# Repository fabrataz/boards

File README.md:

# boards

You'll find here various kicad projects
## Digital:
* digital/SO16SO18W - breakboard for SMD SOIC-16 and SOIC-18W circuits.

## Analog: 
* analog/arpege  - schematic of active electronics (for Passion and Arpege guitars)

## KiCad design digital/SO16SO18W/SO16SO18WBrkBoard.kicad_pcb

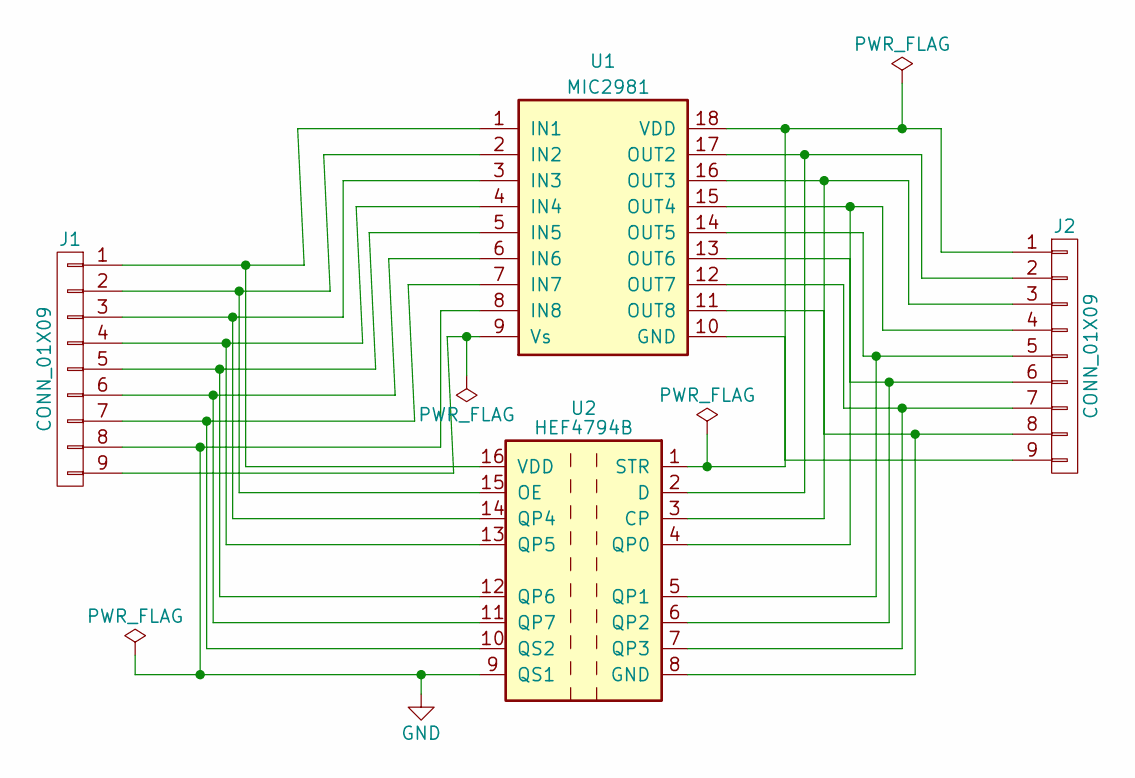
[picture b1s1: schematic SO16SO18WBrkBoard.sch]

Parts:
J1, J2: CONN_01X09; Pin_Header_Straight_1x09_Pitch2.54mm
U1: MIC2981; SOIC-18W_7.5x11.6mm_Pitch1.27mm
U2: HEF4794B; SOIC-16_3.9x9.9mm_Pitch1.27mm

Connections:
GND: J1.8, U1.8 (IN8), U2.9 (QS1)
unnamed: J1.1, U1.1 (IN1), U2.16 (VDD)
unnamed: J1.2, U1.2 (IN2), U2.15 (OE)
unnamed: J1.3, U1.3 (IN3), U2.14 (QP4)
unnamed: J1.4, U1.4 (IN4), U2.13 (QP5)
unnamed: J1.5, U1.5 (IN5), U2.12 (QP6)
unnamed: J1.6, U1.6 (IN6), U2.11 (QP7)
unnamed: J1.7, U1.7 (IN7), U2.10 (QS2)
unnamed: J1.9, U1.9 (Vs)
unnamed: J2.1, U1.18 (VDD), U2.1 (STR)
unnamed: J2.2, U1.17 (OUT2), U2.2 (D)
unnamed: J2.3, U1.16 (OUT3), U2.3 (CP)
unnamed: J2.4, U1.15 (OUT4), U2.4 (QP0)
unnamed: J2.5, U1.14 (OUT5), U2.5 (QP1)
unnamed: J2.6, U1.13 (OUT6), U2.6 (QP2)
unnamed: J2.7, U1.12 (OUT7), U2.7 (QP3)
unnamed: J2.8, U1.11 (OUT8), U2.8 (GND)
unnamed: J2.9, U1.10 (GND)

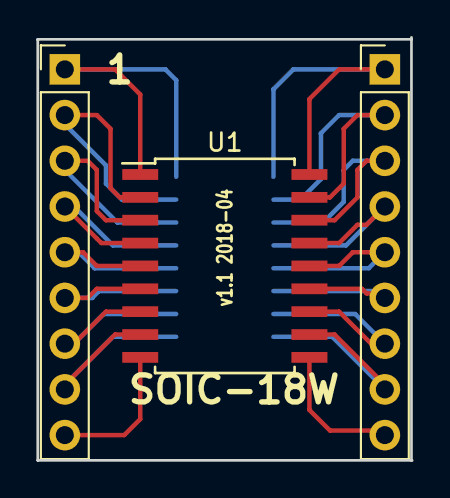
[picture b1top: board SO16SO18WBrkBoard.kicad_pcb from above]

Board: 2 copper layers, 20.8 x 23.5 mm, 4 parts (1 on the bottom side), 18 nets.

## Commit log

2018-04-14 first commit (github)
2018-04-14 Updated Readme, added Project SO16SO18W
2018-04-14 fixed typo
2018-04-14 SO16SO18W - fixed header spacing
2018-04-16 fixed typo in README...
2019-01-19 Added Analog/arpege schematic
2019-01-19 cleanup
2019-01-19 edit README
2019-01-19 added arpege schematic
2019-01-19 Added arpge schematic
2019-01-19 fixed typo in readme
2019-01-19 second attempt
2019-01-19 added schematic image
2019-01-19 added image in README
2019-01-20 added some components values, clean up edge connector
2019-01-20 added notes / labels to booster switch signals
2019-03-17 updated POT values (EQ, tone)
